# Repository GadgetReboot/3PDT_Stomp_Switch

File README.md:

# 3PDT_Stomp_Switch
Guitar Stomp Switch Breakout Board 3PDT  9 pin

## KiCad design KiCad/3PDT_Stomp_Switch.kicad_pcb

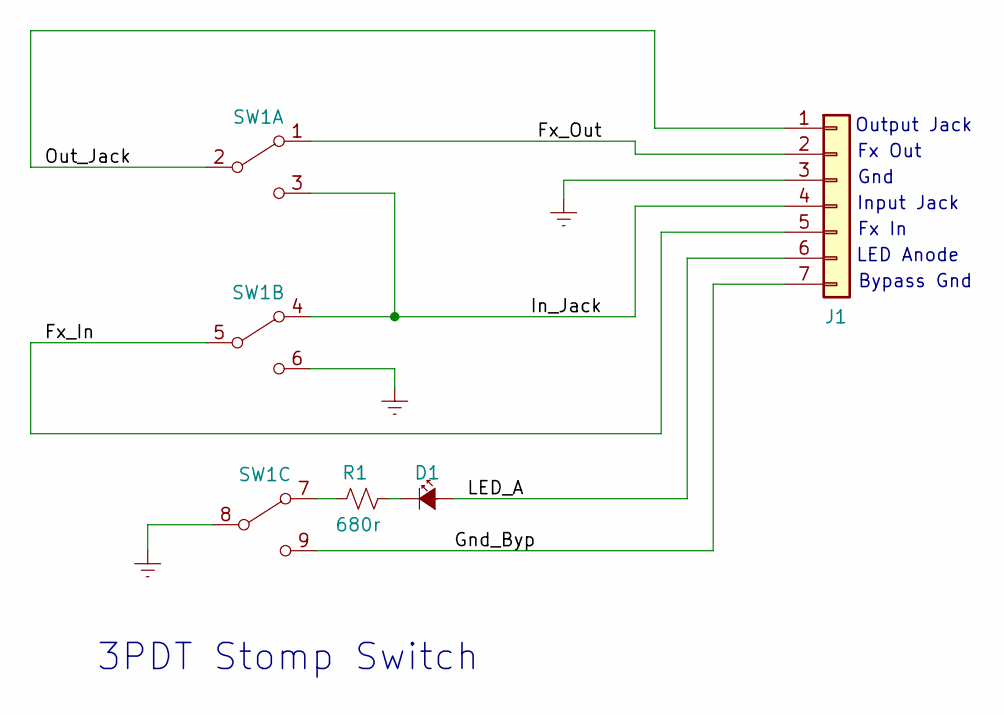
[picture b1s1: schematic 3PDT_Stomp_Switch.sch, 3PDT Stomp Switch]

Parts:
D1: LED_Small_ALT; LED_D5.0mm
J1: Conn_01x07; PinHeader_1x07_P2.54mm_Vertical
R1: 680r; R_Axial_DIN0207_L6.3mm_D2.5mm_P10.16mm_Horizontal
SW1: SW_3PDT; STOMP-SWITCH-3PDT

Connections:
/Fx_In: J1.5, SW1.5 (B)
/Fx_Out: J1.2, SW1.1 (A)
/Gnd_Byp: J1.7, SW1.9 (C)
/In_Jack: J1.4, SW1.3 (C), SW1.4 (A)
/LED_A: D1.2 (A), J1.6
/Out_Jack: J1.1, SW1.2 (B)
GNDREF: J1.3, SW1.6 (C), SW1.8 (B)
unnamed: D1.1 (K), R1.1
unnamed: R1.2, SW1.7 (A)

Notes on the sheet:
3PDT Stomp Switch
Gnd
Input Jack
Fx In
Fx Out
Output Jack
LED Anode
Bypass Gnd

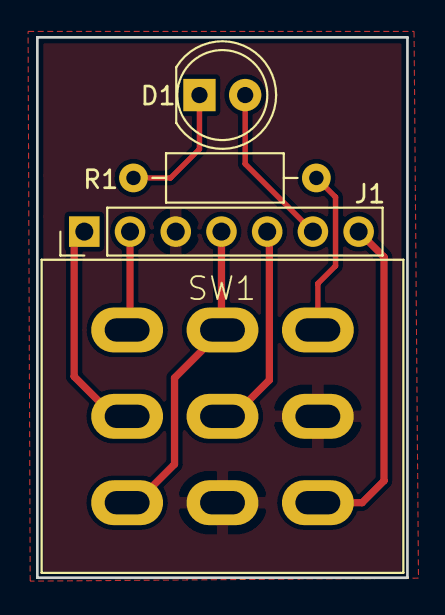
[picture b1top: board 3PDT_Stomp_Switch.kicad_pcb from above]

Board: 2 copper layers, 20.6 x 30.0 mm, 4 parts (0 on the bottom side), 9 nets.
